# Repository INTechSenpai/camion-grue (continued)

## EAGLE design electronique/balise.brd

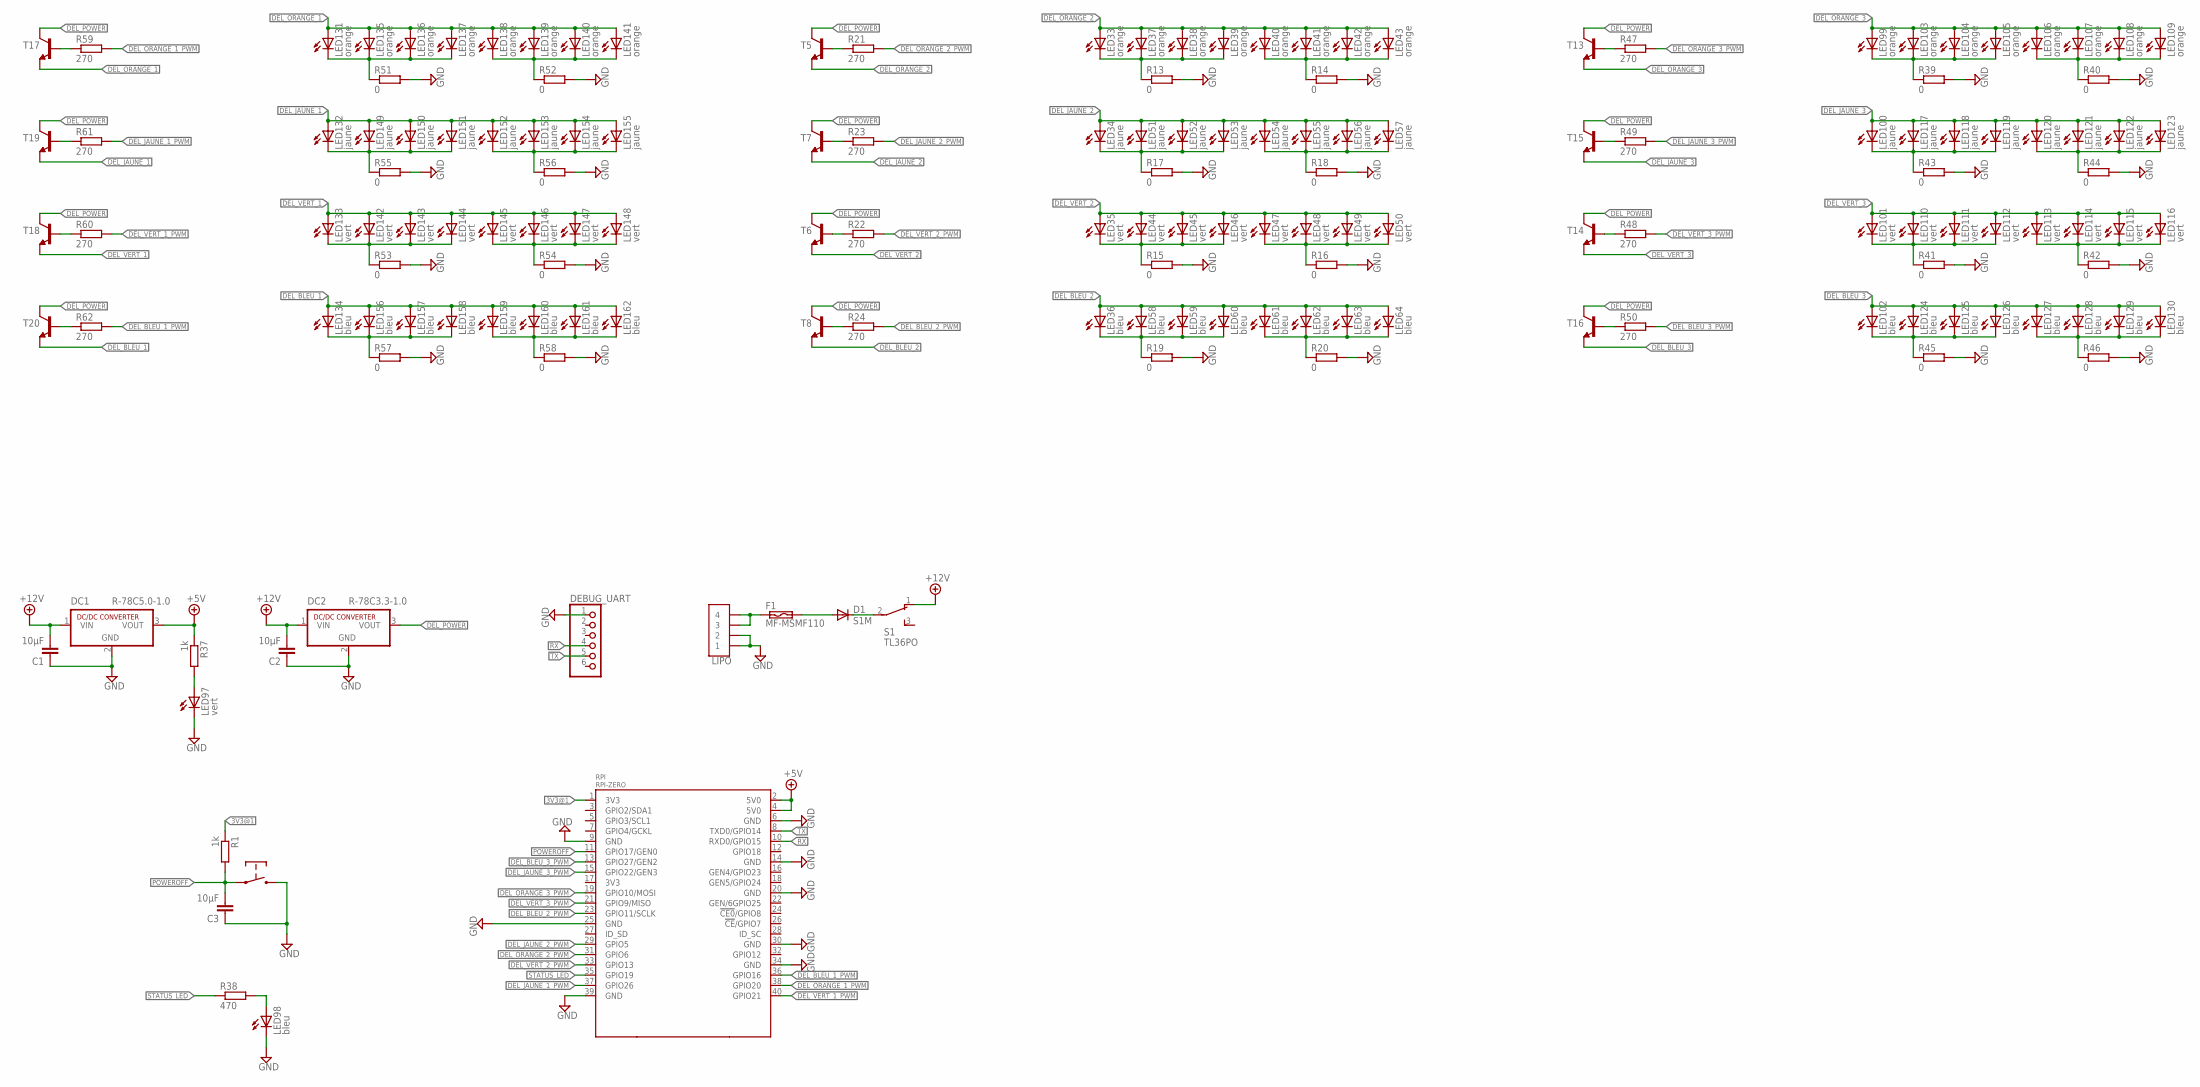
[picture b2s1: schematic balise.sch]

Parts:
C1, C2, C3: 10µF; C0805
D1: S1M; SMA
DC1: R-78C5.0-1.0; SIP3
DC2: R-78C3.3-1.0; SIP3
DEBUG_UART: PINHD-1X6; 1X06
F1: MF-MSMF110
LED33, LED37, LED38, LED39, LED40, LED41, LED42, LED43, LED99, LED103, LED104, LED105, LED106, LED107, LED108, LED109, LED131, LED135, LED136, LED137, LED138, LED139, LED140, LED141: orange; LED5MM
LED34, LED51, LED52, LED53, LED54, LED55, LED56, LED57, LED100, LED117, LED118, LED119, LED120, LED121, LED122, LED123, LED132, LED149, LED150, LED151, LED152, LED153, LED154, LED155: jaune; LED5MM
LED35, LED44, LED45, LED46, LED47, LED48, LED49, LED50, LED97, LED101, LED110, LED111, LED112, LED113, LED114, LED115, LED116, LED133, LED142, LED143, LED144, LED145, LED146, LED147, LED148: vert; LED5MM
LED36, LED58, LED59, LED60, LED61, LED62, LED63, LED64, LED98, LED102, LED124, LED125, LED126, LED127, LED128, LED129, LED130, LED134, LED156, LED157, LED158, LED159, LED160, LED161, LED162: bleu; LED5MM
LIPO: JST-04GH-V; GH-04-V
R1, R37: 1k; R0805
R13, R14, R15, R16, R17, R18, R19, R20, R39, R40, R41, R42, R43, R44, R45, R46, R51, R52, R53, R54, R55, R56, R57, R58: 0; R0805
R21, R22, R23, R24, R47, R48, R49, R50, R59, R60, R61, R62: 270; R0805
R38: 470; R0805
RPI: RPI-ZERO; RASPBERRYPI_BASTELSTUBE_V13_RASPI_BOARD_B+_FULL
S1: TL36PO; TL3XPO
T5, T6, T7, T8, T13, T14, T15, T16, T17, T18, T19, T20: BC817-16-NPN-SOT23-BEC; SOT23-BEC
U$1: PUSH-BUTTON

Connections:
3V3@1: R1.1, RPI.1 (3V3)
+5V: DC1.3 (VOUT), R37.1, RPI.2 (5V0), RPI.4 (5V0)
+12V: C1.2, C2.2, DC1.1 (VIN), DC2.1 (VIN), S1.1 (O)
DEL_BLEU_1: LED134.A, LED156.A, LED157.A, LED158.A, LED159.A, LED160.A, LED161.A, LED162.A, T20.E
DEL_BLEU_1_PWM: R62.2, RPI.36 (GPIO16)
DEL_BLEU_2: LED36.A, LED58.A, LED59.A, LED60.A, LED61.A, LED62.A, LED63.A, LED64.A, T8.E
DEL_BLEU_2_PWM: R24.2, RPI.23 (GPIO11/SCLK)
DEL_BLEU_3: LED102.A, LED124.A, LED125.A, LED126.A, LED127.A, LED128.A, LED129.A, LED130.A, T16.E
DEL_BLEU_3_PWM: R50.2, RPI.13 (GPIO27/GEN2)
DEL_JAUNE_1: LED132.A, LED149.A, LED150.A, LED151.A, LED152.A, LED153.A, LED154.A, LED155.A, T19.E
DEL_JAUNE_1_PWM: R61.2, RPI.37 (GPIO26)
DEL_JAUNE_2: LED34.A, LED51.A, LED52.A, LED53.A, LED54.A, LED55.A, LED56.A, LED57.A, T7.E
DEL_JAUNE_2_PWM: R23.2, RPI.29 (GPIO5)
DEL_JAUNE_3: LED100.A, LED117.A, LED118.A, LED119.A, LED120.A, LED121.A, LED122.A, LED123.A, T15.E
DEL_JAUNE_3_PWM: R49.2, RPI.15 (GPIO22/GEN3)
DEL_ORANGE_1: LED131.A, LED135.A, LED136.A, LED137.A, LED138.A, LED139.A, LED140.A, LED141.A, T17.E
DEL_ORANGE_1_PWM: R59.2, RPI.38 (GPIO20)
DEL_ORANGE_2: LED33.A, LED37.A, LED38.A, LED39.A, LED40.A, LED41.A, LED42.A, LED43.A, T5.E
DEL_ORANGE_2_PWM: R21.2, RPI.31 (GPIO6)
DEL_ORANGE_3: LED99.A, LED103.A, LED104.A, LED105.A, LED106.A, LED107.A, LED108.A, LED109.A, T13.E
DEL_ORANGE_3_PWM: R47.2, RPI.19 (GPIO10/MOSI)
DEL_POWER: DC2.3 (VOUT), T5.C, T6.C, T7.C, T8.C, T13.C, T14.C, T15.C, T16.C, T17.C, T18.C, T19.C, T20.C
DEL_VERT_1: LED133.A, LED142.A, LED143.A, LED144.A, LED145.A, LED146.A, LED147.A, LED148.A, T18.E
DEL_VERT_1_PWM: R60.2, RPI.40 (GPIO21)
DEL_VERT_2: LED35.A, LED44.A, LED45.A, LED46.A, LED47.A, LED48.A, LED49.A, LED50.A, T6.E
DEL_VERT_2_PWM: R22.2, RPI.33 (GPIO13)
DEL_VERT_3: LED101.A, LED110.A, LED111.A, LED112.A, LED113.A, LED114.A, LED115.A, LED116.A, T14.E
DEL_VERT_3_PWM: R48.2, RPI.21 (GPIO9/MISO)
GND: C1.1, C2.1, C3.1, DC1.2 (GND), DC2.2 (GND), DEBUG_UART.1, LED97.K (C), LED98.K (C), LIPO.1, LIPO.2, R13.2, R14.2, R15.2, R16.2, R17.2, R18.2, R19.2, R20.2, R39.2, R40.2, R41.2, R42.2, R43.2, R44.2, R45.2, R46.2, R51.2, R52.2, R53.2, R54.2, R55.2, R56.2, R57.2, R58.2, RPI.6 (GND), RPI.9 (GND), RPI.14 (GND), RPI.20 (GND), RPI.25 (GND), RPI.30 (GND), RPI.34 (GND), RPI.39 (GND), U$1.3, U$1.4
unnamed: F1.1, LIPO.3, LIPO.4
unnamed: D1.A, F1.2
unnamed: D1.C, S1.2
unnamed: LED33.K (C), LED37.K (C), LED38.K (C), LED39.K (C), R13.1
unnamed: LED40.K (C), LED41.K (C), LED42.K (C), LED43.K (C), R14.1
unnamed: LED35.K (C), LED44.K (C), LED45.K (C), LED46.K (C), R15.1
unnamed: LED47.K (C), LED48.K (C), LED49.K (C), LED50.K (C), R16.1
unnamed: LED34.K (C), LED51.K (C), LED52.K (C), LED53.K (C), R17.1
unnamed: LED54.K (C), LED55.K (C), LED56.K (C), LED57.K (C), R18.1
unnamed: LED36.K (C), LED58.K (C), LED59.K (C), LED60.K (C), R19.1
unnamed: LED61.K (C), LED62.K (C), LED63.K (C), LED64.K (C), R20.1
unnamed: R21.1, T5.B
unnamed: R22.1, T6.B
unnamed: R23.1, T7.B
unnamed: R24.1, T8.B
unnamed: LED97.A, R37.2
unnamed: LED98.A, R38.2
unnamed: LED99.K (C), LED103.K (C), LED104.K (C), LED105.K (C), R39.1
unnamed: LED106.K (C), LED107.K (C), LED108.K (C), LED109.K (C), R40.1
unnamed: LED101.K (C), LED110.K (C), LED111.K (C), LED112.K (C), R41.1
unnamed: LED113.K (C), LED114.K (C), LED115.K (C), LED116.K (C), R42.1
unnamed: LED100.K (C), LED117.K (C), LED118.K (C), LED119.K (C), R43.1
unnamed: LED120.K (C), LED121.K (C), LED122.K (C), LED123.K (C), R44.1
unnamed: LED102.K (C), LED124.K (C), LED125.K (C), LED126.K (C), R45.1
unnamed: LED127.K (C), LED128.K (C), LED129.K (C), LED130.K (C), R46.1
unnamed: R47.1, T13.B
unnamed: R48.1, T14.B
unnamed: R49.1, T15.B
unnamed: R50.1, T16.B
unnamed: LED131.K (C), LED135.K (C), LED136.K (C), LED137.K (C), R51.1
unnamed: LED138.K (C), LED139.K (C), LED140.K (C), LED141.K (C), R52.1
unnamed: LED133.K (C), LED142.K (C), LED143.K (C), LED144.K (C), R53.1
unnamed: LED145.K (C), LED146.K (C), LED147.K (C), LED148.K (C), R54.1
unnamed: LED132.K (C), LED149.K (C), LED150.K (C), LED151.K (C), R55.1
unnamed: LED152.K (C), LED153.K (C), LED154.K (C), LED155.K (C), R56.1
unnamed: LED134.K (C), LED156.K (C), LED157.K (C), LED158.K (C), R57.1
unnamed: LED159.K (C), LED160.K (C), LED161.K (C), LED162.K (C), R58.1
unnamed: R59.1, T17.B
unnamed: R60.1, T18.B
unnamed: R61.1, T19.B
unnamed: R62.1, T20.B
POWEROFF: C3.2, R1.2, RPI.11 (GPIO17/GEN0), U$1.1, U$1.2
RX: DEBUG_UART.4, RPI.10 (RXD0/GPIO15)
STATUS_LED: R38.1, RPI.35 (GPIO19)
TX: DEBUG_UART.5, RPI.8 (TXD0/GPIO14)

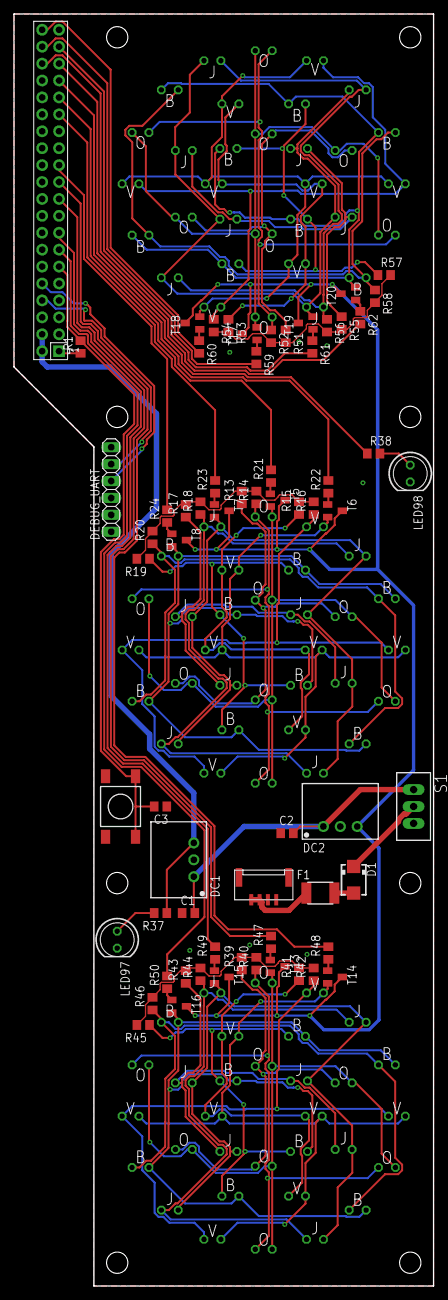
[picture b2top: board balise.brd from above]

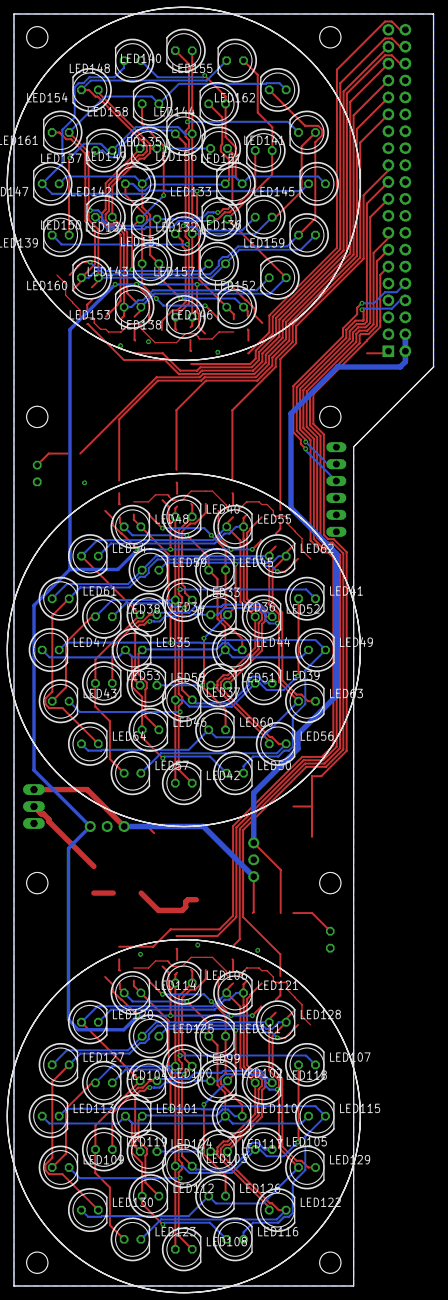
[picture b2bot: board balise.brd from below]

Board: 2 copper layers, 63.0 x 191.0 mm, 161 parts (96 on the bottom side), 74 nets.

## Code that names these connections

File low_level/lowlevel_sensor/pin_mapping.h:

#ifndef _PIN_MAPPING_h
#define _PIN_MAPPING_h

/* ToF sensors */
#define PIN_EN_TOF_AVG      2
#define PIN_EN_TOF_AV       7
#define PIN_EN_TOF_AVD      8
#define PIN_EN_TOF_FLAN_AVG 17
#define PIN_EN_TOF_FLAN_AVD 11
#define PIN_EN_TOF_FLAN_ARG 16
#define PIN_EN_TOF_FLAN_ARD 12
#define PIN_EN_TOF_ARG      15
#define PIN_EN_TOF_ARD      14


/* LEDs */
#define PIN_DEL_CLIGNO_G    10
#define PIN_DEL_CLIGNO_D    20
#define PIN_DEL_NUIT_AV     9
#define PIN_DEL_NUIT_AR     21
#define PIN_DEL_STOP        22
#define PIN_DEL_RECUL       23
#define PIN_DEL_GYRO_1      6
#define PIN_DEL_GYRO_2      5
#define PIN_DEL_GYRO_3      4
#define PIN_DEL_GYRO_4      3

#endif

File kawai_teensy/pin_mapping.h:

#ifndef _PIN_MAPPING_h
#define _PIN_MAPPING_h

/* Encodeurs arrières */
#define PIN_A_RIGHT_BACK_ENCODER	13
#define PIN_B_RIGHT_BACK_ENCODER	14
#define PIN_B_LEFT_BACK_ENCODER		16
#define PIN_A_LEFT_BACK_ENCODER		15


/* Encodeurs des moteurs de propultion */
#define PIN_B_LEFT_MOTOR_ENCODER	8
#define PIN_A_LEFT_MOTOR_ENCODER	7
#define PIN_A_RIGHT_MOTOR_ENCODER	11
#define PIN_B_RIGHT_MOTOR_ENCODER	12


/* Ponts en H des moteurs de propultion */
#define PIN_LEFT_MOTOR_A		3
#define PIN_RIGHT_MOTOR_A		4
#define PIN_LEFT_MOTOR_B		5
#define PIN_RIGHT_MOTOR_B		6


/* Ponts en H des moteurs du filet */
#define PIN_VENTILATEUR		17
#define PIN_MOTOR_NET		20
#define PIN_RIGHT_MOTOR_NET	22
#define PIN_LEFT_MOTOR_NET	23
#define PIN_NET_COM			21

/* Capteurs fin de course du filet */
#if defined(__MK64FX512__) || defined(__MK66FX1M0__) // Teensy 3.5 ou 3.6
#define PIN_BUTEE_G			A22
#define PIN_BUTEE_D			A21
#elif defined(__MK20DX128__) || defined(__MK20DX256__) // Teensy 3.0 3.1 ou 3.2
#define PIN_BUTEE_G			67
#define PIN_BUTEE_D			66
#endif


/* Capteurs ToF : pin 'enable' */
#define PIN_TOF_FLAN_AV_G	24
#define PIN_TOF_FLAN_AR_G	25
#define PIN_TOF_PHARE_AV_G	26
#define PIN_TOF_FRONT		27
#define PIN_TOF_PHARE_AV_D	28
#define PIN_TOF_FLAN_AR_D	31
#define PIN_TOF_FLAN_AV_D	32
#define PIN_TOF_PHARE_AR_D	33
#define PIN_TOF_BACK		34
#define PIN_TOF_PHARE_AR_G	39


/* DELs */
#define PIN_DEL_STATUS_1	2
#define PIN_DEL_STATUS_2	29
#define PIN_FEUX_NUIT		30
#define PIN_CLIGNOTANT_D	35
#define PIN_FEUX_FREIN		36
#define PIN_CLIGNOTANT_G	37
#define PIN_FEUX_RECUL		38


/* Divers capteurs */
#if defined(__MK64FX512__) || defined(__MK66FX1M0__) // Teensy 3.5 ou 3.6
#define PIN_GET_COLOR		A25
#elif defined(__MK20DX128__) || defined(__MK20DX256__) // Teensy 3.0 3.1 ou 3.2
#define PIN_GET_COLOR		68
#endif
#define PIN_GET_VOLTAGE		A11
#define PIN_GET_JUMPER		A10


#endif

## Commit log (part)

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2018-01-05 Ajout libs Eagle
2018-01-05 maj elec et libs eagle
2018-01-07 Elec: schéma presque ok + placement des composants
2018-01-08 Début de routage...
2018-01-09 ajout carte elec grue
2018-01-10 Ajout lib Eagle DC-DC-converter
2018-01-10 Elec: routage catre principale presque fini !
2018-01-11 Elec cockpit terminée
2018-01-12 Comment ça il n'y a plus de pins dispo ? mais enfin tout va bien !
2018-01-13 L'élec ça c'est fait !
2018-01-15 ajout de la doc série
2018-01-16 BlockingQueue in IncomingBuffer
2018-01-16 Logique de communication révisée
2018-01-16 Configuration de la communication ethernet
2018-01-16 Stream trop long à être éteint : une durée max plutôt qu'un nombre de message
2018-01-16 Reconnexion ethernet
2018-01-16 Architecture pour série de secours
2018-01-16 Protocole de communication
2018-01-17 Scripts pour la raspi
2018-01-17 Ajout d'une communication série dans le HL
2018-01-17 Fichiers de configurations
2018-01-19 Elec: ajout doc
2018-01-19 Elec balise: un bon début :)
2018-01-20 Communication Éthernet opérationnelle
2018-01-20 Fermeture propre du thread d'écoute
2018-01-20 Ajout OrderMgr pour faire des pings pour de vrai ! Et plus si affinités...
2018-01-21 Le HL ignore les trames d'information
2018-01-21 Beaucoup de debug un peu partout
2018-01-21 Suppression de config inutile
2018-01-21 Test déconnexion
2018-01-22 maj elec balise
2018-01-22 LL: bugfix message d'erreur intempestif
2018-01-22 Config pour ignorer le test de latence
2018-01-26 pom.xml
2018-02-03 Ajout élec balise
2018-02-03 Elec balise routée !
2018-02-04 Elec version finale + Ajout fichiers gerber
2018-02-04 Elec: début de liste de courses
2018-02-13 Communication de float en binaire entre LL et HL
2018-02-14 Rename BinaryComm to FloatBinaryEncoder
2018-02-14 Correction encodage UTF-8
2018-02-16 Sauvegarde du code LL avant de tout casser
2018-02-16 Revert "Sauvegarde du code LL avant de tout casser"
    This reverts commit 21cdad873b082bdfab5906957f14ebadb3b6825d.
2018-02-16 Déco / reco opérationnel (en utilisant la lib corrigée)
2018-03-09 Submodules en https et pas ssh
2018-03-10 Amélioration de la gesion des erreurs d'AX12
2018-03-17 Mise à jour protocole
2018-03-17 Quelques ajustements des ordres
2018-03-17 Mise à jour du protocole
2018-03-17 int32 à la place de uint32 dans le protocole
2018-03-17 Nouvelle gestion du code de retour de FOLLOW_TRAJECTORY
2018-03-20 add compatibility for Arduino IDE
2018-03-20 MAJ protocole-ordres
2018-03-20 Mise à jour du script all_update.sh
2018-03-20 Maj protocole LL-HL dans l'interface de débug
2018-03-20 Lowlevel: architecture setup and first tests
2018-03-22 LL debug interface: optimisations
2018-03-24 Création facile de trajectoire
2018-03-24 Mise à jour du protocole d'envoi d'arcs
2018-03-24 Arrêt propre
2018-03-24 Script d'upload sur raspi
2018-03-24 Update travis file
2018-03-24 Debug&optimized lowlevel_debug interface + implementation of (almost) all orders
2018-03-24 Les chemins sont sauvegardés dans une structure
2018-03-24 La vidéo doit être centrée sur le robot en mode zoom
2018-03-24 Appel au destructeur graphique
2018-03-25 Mise à jour lib graphique
2018-03-25 Add default config file
2018-03-25 N'affiche plus le nom du dernier commit
2018-03-27 Affiche la configuration des sous-projets aussi
2018-03-30 Thread d'échauffement de la JVM
2018-03-30 Les threads sont des démons
2018-03-30 Script pour construire des trajectoires XY ou XYO
2018-03-30 Benchmark pour XYO aussi
2018-03-31 Suppression de trucs qui servent à rien pour le moment
2018-03-31 Un ticket peut maintenant contenir n'importe quelles données
2018-03-31 Peut demander le niveau de batterie au LL
2018-03-31 Utilise en loucedé le DefaultCheminPathfinding de Kraken
2018-04-01 Add benchmark script
2018-04-01 Fichier de conf pour le warmup
2018-04-01 Image robot
2018-04-01 Mise à jour config
2018-04-01 .gitignore update
2018-04-01 Remove target/classes
2018-04-01 Lowlevel debug tools: fully working version with almost all the needed features
2018-04-01 Lowlevel master: working version with only locomotion
2018-04-01 lowlevel sensor: test code for sensors and LEDs
2018-04-01 Maj root .gitignore
2018-04-01 Maj des gitignore, en mieux, beaucoup mieux
2018-04-02 Config par défaut changée
2018-04-02 Communication en little endian
2018-04-02 maj format des données capteurs
2018-04-02 Table simplifiée + affichage
2018-04-02 Début de scripts
2018-04-02 Les obstacles dynamiques contiennent maintenant les éléments de la table
2018-04-02 update submodule dynamixel_teensy
2018-04-02 Lowlevel cleanup and better logs
2018-04-03 Liens relatifs pour les scripts
2018-04-03 Affiche toujours les warnings et les criticals
2018-04-03 Inclut les images dans le .jar
2018-04-03 Mise à jour des fichiers de config
2018-04-03 *.conf plus ignorés
2018-04-03 Scripts gpio
2018-04-03 Bugfix script GPIO
2018-04-03 Diode allumée = HL tourne (à tester)
2018-04-03 Fichier de test
2018-04-03 Doc prise cube
2018-04-04 Arrêt gpio : allume la diode et éteint le HL
2018-04-04 La diode clignote 5s lorsque le HL a une erreur fatale
2018-04-04 Arrêt beaucoup plus propre
2018-04-04 Gestion de l'arrêt du HL
2018-04-04 LL: DEL manager is here !
2018-04-04 Scripts (WIP)
2018-04-04 Lowlevel: internal communication utilities (WIP)
2018-04-05 LL internal com WIP
2018-04-06 Màj API Kraken
2018-04-06 Architecture éléments de jeu
2018-04-06 Mise à jour année copyright
2018-04-06 Gestion de la symétrie pour la prise de cube
2018-04-06 Utilitaire pour cubes
2018-04-08 Mise à jour gpio_halt.sh
2018-04-08 VideoReader (WIP)
2018-04-09 Traitement des capteurs + initialisation position robot
2018-04-10 Peut limiter la vitesse des chemins déjà enregistrés
2018-04-10 Mise à jour Kraken
2018-04-11 Update Kraken
2018-04-11 Set theme jekyll-theme-midnight
2018-04-11 Page GitHub
2018-04-11 Modification protocole
2018-04-11 Mise à jour protocole HL
2018-04-12 Les libs HL sont maintenant hébergées sur packagecloud
2018-04-12 Fix pom.xml
2018-04-15 Interfaçage avec Kraken pour la replanification
2018-04-15 Préparation du code des actionneurs
2018-04-15 Code grue v1 ! tout bouge, dans le bon sens, reste plus qu'à régler l'asservissement pour un bonheur maximal
2018-04-15 Nouveau navmesh
2018-04-16 bugfix + asserv grue
2018-04-17 Utilisation automatique des chemins déjà trouvés (WIP)
2018-04-17 Mise à jour version de Kraken utilisée
2018-04-18 On utilise le plus court chemin mémorisé
2018-04-18 Chemin symétrisé automatiquement
2018-04-18 Plus de log pour les chemins enregistrés
2018-04-18 Maj doc LL ordres grue
2018-04-19 On vérifie quand même les collisions en mode dégradé…
2018-04-19 Package management
2018-04-19 Possibilité de désactiver l'utilisation de chemins enregistrés
2018-04-19 Fix utilisation de chemins connus
2018-04-19 Bugfix cube
2018-04-19 Wololooo
2018-04-19 LL: implementation séquences de mouvements de grue
2018-04-22 Mise en ligne de l'affiche du robot
2018-04-22 LL grue: implem commandes + ajout commande manuelle
2018-04-23 LL grue: communication avec master implémentée
2018-04-26 amélioration contrôle manuel et affichage 7 seg
2018-04-27 implémentation des ordres HL (non testé)
2018-04-27 LL: Ajout procédure de pose de cube
2018-04-29 Petite doc pour la LED
2018-04-29 Clignotement lent quand le HL est démarré
2018-04-29 Réglages d'angles du bras
2018-04-29 Ajout code retour actionneur TIMEOUT
2018-04-29 Implémentation protocole actionnneurs (WIP)
2018-04-29 Script prise de cube + arrêt final
2018-04-29 Scripts triés par proximité
2018-04-29 LL: maj script dépose cube
2018-04-29 On ne prend que les cubes de notre côté
2018-04-29 Script dépose
2018-05-01 Thread de détection de sous-tension
2018-05-01 Avec le fichier en plus c'est mieux…
2018-05-01 LL: petits ajustements
2018-05-02 Chemins enregistrés
2018-05-02 Utilitaire pour suivre une trajectoire
2018-05-02 Plus de forkbomb =(
2018-05-02 On spamme plus de STOP le LL + buffer capteur plus petit
2018-05-02 Vérification de la latence de traitement des données du LL
2018-05-02 Bugfix protocole
2018-05-02 Jumper + bugfix
2018-05-03 Les tourelles ignorent les obstacles trop proches du robot
2018-05-03 Support XL320 tourelle + ToF longue portée + augmentation de portée des ToF courte portée
2018-05-03 Update protocole + visée tourelles HL
2018-05-03 Ajout fichiers + bugfix angle tourelle
2018-05-03 Bugfix utilisation actionneurs
2018-05-03 On ne spamme plus les tourelles
2018-05-03 Bugfix évitement pendant qu'on avance
2018-05-04 LL: Ajustements tourelles + débug ordre storeCubeInside
2018-05-04 LL: ajout des feux contextuels + amélioration lecture capteurs tourelle
2018-05-04 Définitivement plus de replanification
2018-05-04 On retire les cubes de la demi-table adverse
2018-05-04 Réécriture des obstacles de proximité
2018-05-04 Bugfix collision de détection
2018-05-05 Peut désactiver la tourelle depuis la config
2018-05-05 On désactive le thread de commande de tourelles si elles sont désactivées
2018-05-05 Correction XYO statique et dynamique
2018-05-05 Optimisation mémoire
2018-05-05 Bugfix initialisation position + traitement tourelle
2018-05-05 Capteurs tourelle: renvoient DEAD lorsque la tourelle tourne; Ajout de Logs Série sur la Teensy DELs&capteurs pour visualiser les données ToF courte portée
2018-05-05 Add wiimote controler script from moon-rover
2018-05-05 Avec tous les fichiers
2018-05-05 Position moins verbeuse
2018-05-05 Script recalage
2018-05-05 Bugfix détection de collision
2018-05-05 Correction d'odo
2018-05-05 Script match
2018-05-05 Mode télécommande WIP
2018-05-05 LL actuator: add debug LEDs for mysterious bug tracking
2018-05-05 La distance au script de prise de cube dépend aussi de l'orientation
2018-05-05 Pattern en paramètre
2018-05-05 Obstacle pour les piles une fois déposées
2018-05-06 Marge bord pour Kraken, bugfix script
2018-05-06 Script domotique v2
2018-05-06 Script faisable ou non
2018-05-06 Scripts faisables, suite
2018-05-06 add arm order pushButton
2018-05-06 update LL bug tracker and todo list
2018-05-06 Script domotique + correction
2018-05-06 LL meilleure gestion des erreurs au sein des scripts du bras
2018-05-07 Faisabilité de scripts
2018-05-07 Scripts
2018-05-07 Config golden cube
2018-05-07 Script + détection de couleur
2018-05-07 Plus de pathDegrade
2018-05-07 Marge pour pas rentrer dans les cubes
2018-05-07 Bugfix test
2018-05-07 Code de match
2018-05-07 Bugfix script abeille
2018-05-07 Clignote pas à la fin en cas d'erreur
2018-05-07 rework lib xl-320 WIP
2018-05-07 lib réécrite, à tester
2018-05-07 LL arm: XL320 debug checksum calc + update error handling
2018-05-07 add verbose
2018-05-07 bugfix saturation liaison I2C bras
2018-05-07 maj doc LL com interne
2018-05-07 bugfix error handling qui bloquait tout lol
2018-05-08 Warnings
2018-05-08 Ranger le bras du bon côté
2018-05-08 Verbose + bugfix script dépose
2018-05-08 On ne vérifie que le CUBE_MISSED pour take cube
2018-05-08 MAJ ordres bras + peaufinage des scripts LL associés
2018-05-08 Script avec une seule pile
2018-05-08 Script abeille + depose cube
2018-05-08 On ne panique pas si on voit sa propre pile
2018-05-08 LL bufix des scripts pour ne pas défoncer notre belle pile de cubes :)
2018-05-08 LL fix script takeCube qui pouvait dégager celui stocké
2018-05-08 Bugfix correction
2018-05-08 En cas de MOVE_TIMED_OUT, on réessaie au plus 2 fois
2018-05-08 Dépose intelligente
2018-05-09 Script bugfix bourrine
2018-05-09 Config scripts
2018-05-09 Interrupteur réhaussé
2018-05-09 Vérif de la hauteur de l'interrupteur (WIP)
2018-05-09 Config par défaut
2018-05-09 Script fix
2018-05-09 Paramètres de match
2018-05-09 On retente la dépose directement
2018-05-09 Malus sur la prise des cubes noirs qu'on voit pas bien
2018-05-09 Script abeille
2018-05-10 Bugfix abeille + pushbutton
2018-05-10 Deux arm push button
2018-05-10 Ignore obstacle dans zone de construction
2018-05-10 Repli le bras d'abeille que si on a poussé l'abeille
2018-05-10 Plus de marge sur les capteurs
2018-05-10 Script abeille + prise de cubes
2018-05-10 Verbose
2018-05-10 On retire un peu plus pour bien pousser l'abeille
2018-05-11 Log des matchs 1, 2 et 3
2018-05-11 Pilotage par wiimote
2018-05-12 Log du match 5
2018-05-13 ajout lib XL320 au LL-master
